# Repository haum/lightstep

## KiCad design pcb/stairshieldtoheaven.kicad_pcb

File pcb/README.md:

# Strair Sheeld to heaven 

Sheeld arduino (format R3) pour connecter et piloter une alim ATX de pc.

Le shield comporte aussi des borniers pour acceder a chaque port de l'arduino

Réalisé avec Kicad https://github.com/haum/libs_kicad

Les librairies suplémentaires sont disponible ici  https://github.com/haum/libs_kicad

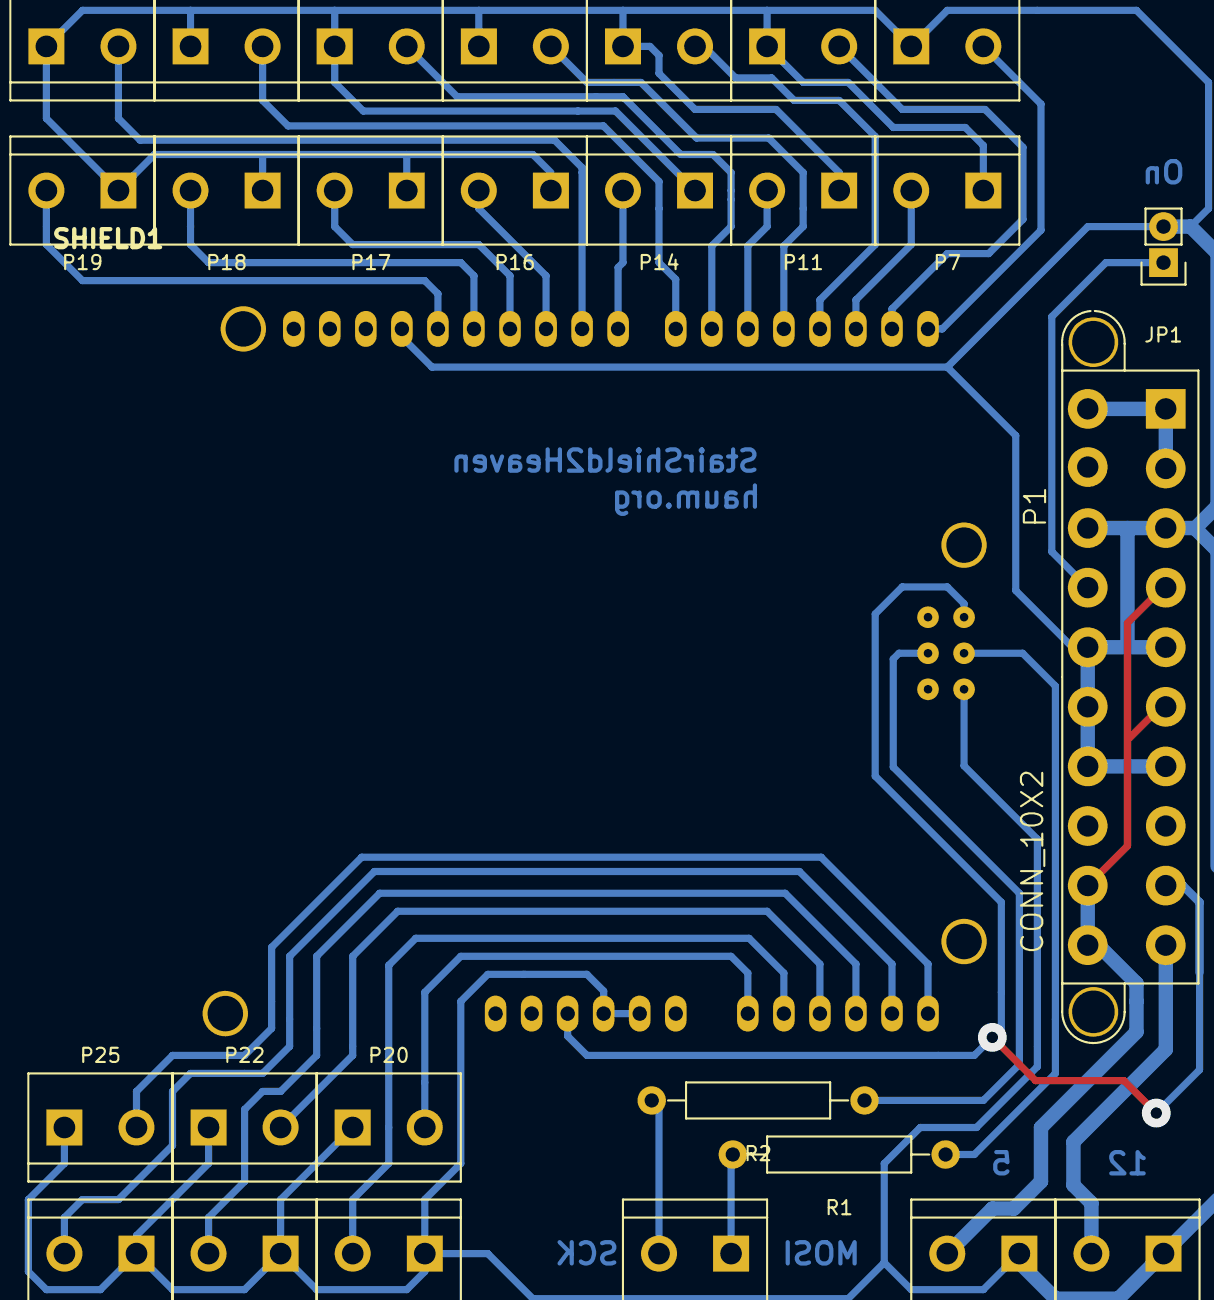
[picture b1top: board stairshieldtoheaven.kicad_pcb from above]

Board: 2 copper layers, 28 parts (0 on the bottom side), 30 nets.

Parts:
JP1: JUMPER; Pin_Header_Straight_1x02
P1: CONN_10X2; ATX20
P2: LED1; bornier2
P4: 5V; bornier2
P5: 1; bornier2
P6: 2; bornier2
P7: 3; bornier2
P8: 4; bornier2
P9: 12V; bornier2
P10: 5; bornier2
P11: 6; bornier2
P12: 7; bornier2
P13: 8; bornier2
P14: 9; bornier2
P15: 10; bornier2
P16: 11; bornier2
P17: 12; bornier2
P18: 13; bornier2
P19: 14; bornier2
P20: 15; bornier2
P21: 16; bornier2
P22: 17; bornier2
P23: 18; bornier2
P24: 19; bornier2
P25: 20; bornier2
R1, R2: R; Resistor_Horizontal_RM15mm
SHIELD1: ARDUINO_SHIELD_R3

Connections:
/1: P5.2, SHIELD1.0
/2: P6.2, SHIELD1.1
/3: P7.2, SHIELD1.2
/3V3: P1.1, P1.2, P1.3
/4: P8.2, SHIELD1.3
/5: P10.2, SHIELD1.4
/5V: P1.7, P1.11, P1.18, P1.20, P4.2
/6: P11.2, SHIELD1.5
/7: P12.2, SHIELD1.6
/8: P13.2, SHIELD1.7
/9: P14.2, SHIELD1.8
/10: P15.2, SHIELD1.9
/11: P16.2, SHIELD1.10
/12: P17.2, SHIELD1.11
/12V: P1.19, P9.2
/13: P18.2, SHIELD1.12
/14: P19.2, SHIELD1.13
/15: P20.2, SHIELD1.AD0
/16: P21.2, SHIELD1.AD1
/17: P22.2, SHIELD1.AD2
/18: P23.2, SHIELD1.AD3
/19: P24.2, SHIELD1.AD4
/20: P25.2, SHIELD1.AD5
/MOSI: R1.1, SHIELD1._MOS
/PSON: JP1.1, P1.8
/SCK: R2.1, SHIELD1._SCK
GND: JP1.2, P1.5, P1.6, P1.9, P1.10, P1.12, P1.13, P1.14, P4.1, P5.1, P6.1, P7.1, P8.1, P9.1, P10.1, P11.1, P12.1, P13.1, P14.1, P15.1, P16.1, P17.1, P18.1, P19.1, P20.1, P21.1, P22.1, P23.1, P24.1, P25.1, SHIELD1.GND1, SHIELD1.GND2, SHIELD1.GND3, SHIELD1._GND
unnamed: P2.1, R1.2
unnamed: P2.2, R2.2
VCC: P1.17, SHIELD1.5V, SHIELD1._5V

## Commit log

2015-10-07 ajout du README
2015-10-07 schema complet
2015-10-07 version1 PCB
2015-10-07 Ajust vias
2015-10-08 simplification connection LED
2015-10-08 mise a jour fichiers de fab
2015-10-08 Ajout pin PowerGood redefinition plan de masse regénération fichiers de fabrication
2015-10-08 Add submodules for firmware
2015-10-08 fw: first ideas & code
2015-10-08 massive rename improved version
2015-10-08 Update schematic and pcb
2015-10-10 correction submodules
2015-10-12 Add missing PCB update
2015-10-13 Fix bad commit: add missing files
2015-10-13 Rename *sheeld* to *shield*
2015-12-07 Start again the firmware without polychrhaum
2015-12-07 ignore build dir
2015-12-08 ajout animation rainbow
2015-12-08 ajout annimation ring
2015-12-08 Fix directory name for utils & typo in files names
2015-12-08 Add K2000 Animation
2015-12-08 Modify files name to remove typo
2015-12-08 Use new file names
2015-12-08 ajout animation rainbow up down
2015-12-09 add struct for jblb LEDs
2015-12-09 update rainbow animation to use jbjb led's struct
2015-12-09 more aninations
2015-12-09 remove PolychrHAUM from Makefile
2015-12-09 update main loop
2015-12-09 fixing error in color change
2015-12-09 improve pulse animation
2015-12-10 Better way to manage differents LED configurations Added a config for jblb led's panel
2015-12-10 update to reflect new config
2015-12-10 garland animations
2015-12-10 change due to config restructuration
2015-12-10 update jblb_led config
2015-12-10 new #define GARLAND_LENGH
2015-12-10 start a new way to handle time in animations
2015-12-10 better way to handle time in anims
2015-12-12 added animations movingup and falling of LED
2015-12-13 Clean dirty code :)
2015-12-13 Clean some code
    Protect headers against multiple inclusion
    Move headers inclusion in implementation instead of headers when relevant
2015-12-13 Fix typo in define
2015-12-13 Run through delays without impacting the LED dithering
    See FastLED doc : https://github.com/FastLED/FastLED/wiki/FastLED-Temporal-Dithering
2015-12-13 Fix pulse using FastLED functions
2015-12-13 Fix JBLB_LED define according to previous commit
2015-12-13 Prefer FastLED dedicated function for LEDs clearing
2015-12-13 Use shortest delay (faster FPS)
2015-12-13 Create Animation class to describe an animation
    Replace changingled (C) to AnimationBreath class (cpp)
2015-12-13 Add a base color to Animation::animate() prototype
2015-12-13 Port K2000 animation to new Animation model class
2015-12-13 Indent code
2015-12-13 Fix typo
2015-12-13 Remove unused code
2015-12-13 Add missing default implementation for Animation::init()
2015-12-13 K2000: clean prescaling
2015-12-13 Port RainbowWipe algo to Animation class model
2015-12-13 Create animation and color choosing mechanism
2015-12-13 Hey, K2000 is an animation
2015-12-14 make K2000 animation with prameters
2015-12-14 change moveup animations in the new way to handle anims
2015-12-14 supress flickering in AnimationMoveUp
2015-12-14 used of native library function
2015-12-15 correction erreur de mapping
2015-12-15 Use 'stairs' instead of 'steps' to talk about stair steps
2015-12-15 Add Framebuffer
2015-12-15 Dead code in comments should never exist
2015-12-15 Change brightness, especially for dev
2015-12-15 Add init method to framebuffer so things doesn't freeze on arduino 105
2015-12-15 Breath: breath on full height
2015-12-15 Breath: breath down shortly
2015-12-15 add anim wipe one column
2015-12-16 use of COLUMNS constants in animations/breath
2015-12-17 Use HSV instead on RGB
2015-12-17 K2000: Fix bounds (use RINGS)
2015-12-17 MagicPoint: add new animation with a moving Point
2015-12-17 Remove wheel.cpp/h
2015-12-17 Include FastLED in animations.h
2015-12-17 Move Point class into dedicated file
2015-12-17 Map all inputs
2015-12-17 Set full brightness
2015-12-17 change point color computation (do not change own brightness)
2015-12-17 Add default alive animation
2015-12-17 Rename MagicPoint to MultiPoints
2015-12-17 Point: add multi-include protection
2015-12-17 Rename K2000 to MagicPoint
2015-12-17 Sort animations in main file
2015-12-17 Add glitter animation -- mind the flashes
2015-12-18 Candy: add new animation
2015-12-18 K2000: add new animation
2015-12-18 MultiPoints: minor animation fixes
2015-12-18 Add remanence animation from Jean-Marc
2015-12-18 Minor fix: add missing comma.
2015-12-18 remove useless dangerous and buggy code
2015-12-18 luz.h: use defines instead of hardcoded values
2015-12-18 Snake: add new animation
2015-12-18 rename rainbowwipe to plumeau
2015-12-18 add strange effect to plumeau
2015-12-18 rework plumeau to use baseColor
2015-12-19 report change in luz in jblb_led
2015-12-19 ajust mapping in jblb_leds
2015-12-22 adjustments
2015-12-22 add watchdog
